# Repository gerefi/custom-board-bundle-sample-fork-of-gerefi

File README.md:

<div align="center">

<b>GPL open-source ECU</b>

</div>

# gerefi

See [check.c](https://github.com/gerefi/gerefi/blob/master/firmware/check.c) for recommended version of GCC.

Current binaries are always available on our [build server](http://gerefi.com/build_server/)

# Cloning the repository
`git clone https://github.com/gerefi/gerefi.git`
Important note - we now use submodules:

`git submodule update --init`

# What do we have here?
 * [Firmware](/firmware) Source code for open source engine control unit for stm32 chips incuding [implementation overview](https://github.com/gerefi/gerefi/blob/master/firmware/readme.md)
 * [Hardware](/hardware) KiCAD files for our older PCBs
 * [gerefi console](/java_console) gerefi own naive tuning software
 * [Simulator](/simulator) win32 or posix version of firmware allows to explore without any hardware 
 * [Unit Tests](/unit_tests) Unit tests of firmware pieces
 * [Misc tools](/java_tools) Misc development utilities
 * [misc/Jenkins](/misc/jenkins) Jenkins Continuous Integration scripts
 * [Software Development process](misc/SoftwareDevelopmentProcess.md)

# External Links

 * [Documentation](https://github.com/gerefi/gerefi/wiki)
 * [Doxygen documentation](http://gerefi.com/docs/html)
 * [General source code Q&A](http://gerefi.com/forum/viewtopic.php?f=5&t=10)
 * [Facebook](https://www.facebook.com/gerefiECU)

# Building the Code
Check out https://gerefi.com/forum/viewtopic.php?f=5&t=9

# Release Notes

See [the changelog](firmware/CHANGELOG.md)

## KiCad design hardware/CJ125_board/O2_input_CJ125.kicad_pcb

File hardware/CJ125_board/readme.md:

[iBom](https://gerefi.com/docs/ibom/O2_input_CJ125_latest.html)

2019 status: known to work, but documentation is very limited :(

On this board UR and UA do NOT have build-in resistor dividers.

There is an opinion that for open air UA divider is required.

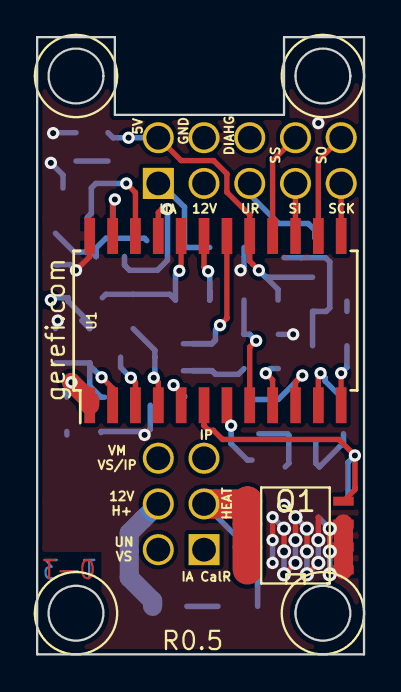
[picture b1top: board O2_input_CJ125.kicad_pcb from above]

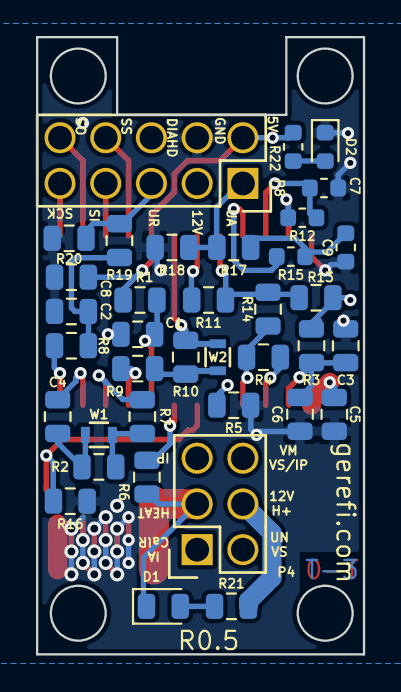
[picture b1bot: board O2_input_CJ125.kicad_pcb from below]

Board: 4 copper layers, 18.2 x 34.3 mm, 39 parts (37 on the bottom side), 35 nets.

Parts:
C1: 1000pF; C_0805_2012Metric
C2, C6, C8: 0.033uF; C_0805_2012Metric
C3: DNP; C_0805_2012Metric
C4: 0.1uF; C_0805_2012Metric
C5: 220pf; C_0805_2012Metric
C7: 0.1uF; C_0603_1608Metric
C9: 0.033uF; C_0603_1608Metric
D1: LED-RED; LED_0805_2012Metric
D2: LED-GRN; LED_0603_1608Metric
P4: CONN_02X03; Socket_Strip_Straight_2x03
P8: CONN_02X05; Socket_Strip_Straight_2x05
Q1: FDS2734; SO8E_ST
R1, R5, R7, R16, R18, R20: 10k; R_0805_2012Metric
R2: 21k6; R_0805_2012Metric
R3: 0R; R_0805_2012Metric
R4: 61.9; R_0805_2012Metric
R6, R17, R19: 6.8k; R_0805_2012Metric
R8: 1k; R_0805_2012Metric
R9: 82.5; R_0805_2012Metric
R10: 220; R_0805_2012Metric
R11: 5.11k; R_0805_2012Metric
R12: 100k; R_0603_1608Metric
R13: 100k; R_0805_2012Metric
R14: 511k; R_0805_2012Metric
R15, R22: 1k; R_0603_1608Metric
R21: 4.7k; R_0805_2012Metric
U1: CJ125; SOIC-24_7.5x15.4mm_Pitch1.27mm
W1, W2: TEST; R_0603

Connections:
/CF: C7.2, R12.1, U1.22
/CJ125_5v: C8.2, P8.2, R1.2, R22.1, U1.17
/CJ125_HEATER: D1.1, P4.3, Q1.2, R6.2
/CJ125_IA: P4.1, R4.2, R14.1, U1.4
/CJ125_IP: P4.5, R4.1, U1.3
/CJ125_SCK: P8.9, U1.13
/CJ125_SI: P8.7, U1.15
/CJ125_SO: P8.10, U1.14
/CJ125_SS: P8.8, U1.16
/CJ125_UA: C9.2, R15.1, R17.2
/CJ125_UN: P4.2, R3.2, R13.1
/CJ125_UR: C2.1, R8.2, R19.2
/CJ125_VM: P4.6, R10.1, U1.18, W2.2
/CM: C4.2, U1.11
/DIAHD: R6.1, U1.7
/DIAHG: P8.6, Q1.1, R16.2, U1.6
/OSZ: R5.2, U1.5
/RF: R12.2, U1.23
/RM: R7.1, U1.10
/RS: R9.2, U1.9
/RST: C1.1, R1.1, U1.8
/UA: R15.2, U1.21
/UN: C3.1, C5.1, R3.1, U1.2
/UP: R11.1, R13.2, R14.2, U1.20
/UR: R8.1, U1.12
/US: R11.2, U1.19
/WO2-12V: C6.2, P4.4, P8.3, R21.2, U1.1
GND: C1.2, C2.2, C3.2, C5.2, C6.1, C7.1, C8.1, C9.1, D2.1, P8.4, Q1.3, R5.1, R16.1, R18.2, R20.2, U1.24
unnamed: C4.1, R2.2, W1.1
unnamed: D1.2, R21.1
unnamed: D2.2, R22.2
unnamed: P8.1, R17.1, R18.1
unnamed: P8.5, R19.1, R20.1
unnamed: R2.1, R7.2, W1.2
unnamed: R9.1, R10.2, W2.1

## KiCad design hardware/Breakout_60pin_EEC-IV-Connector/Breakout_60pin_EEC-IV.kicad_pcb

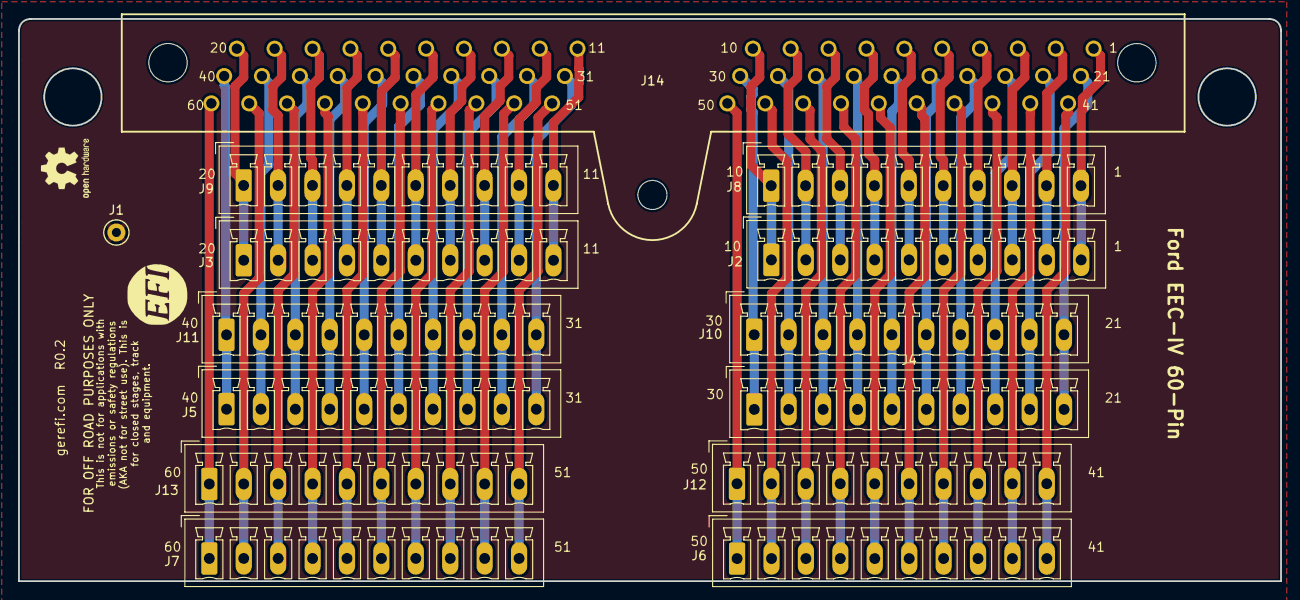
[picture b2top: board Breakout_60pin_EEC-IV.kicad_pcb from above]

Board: 2 copper layers, 139.7 x 62.2 mm, 17 parts (0 on the bottom side), 60 nets.

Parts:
G1: Disclaimer; Off_Road_Disclaimer
G2: LOGO
J1: Conn_01x01; TestPoint_Keystone_5000-5004_Miniature
J2, J3, J4, J5, J6, J7, J8, J9, J10, J11, J12, J13: Conn_01x10; PhoenixContact_MCV_1,5_10-G-3.81_1x10_P3.81mm_Vertical
J14: EEC-IV; eeciv
LOGO1: DNP; OSHW-Logo2_7.3x6mm_SilkScreen

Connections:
/1: J2.10, J8.10, J14.1
/5: J2.6, J8.6, J14.5
/10: J2.1, J8.1, J14.10
/11: J3.10, J9.10, J14.11
/15: J3.6, J9.6, J14.15
/25: J4.6, J10.6, J14.25
/30: J4.1, J10.1, J14.30
/31: J5.10, J11.10, J14.31
/35: J5.6, J11.6, J14.35
/40: J5.1, J11.1, J14.40
/41: J6.10, J12.10, J14.41
/45: J6.6, J12.6, J14.45
/50: J6.1, J12.1, J14.50
/53: J7.8, J13.8, J14.53
/54: J7.7, J13.7, J14.54
/55: J7.6, J13.6, J14.55
/60: J7.1, J13.1, J14.60
/420: J3.1, J9.1, J14.20
/421: J4.10, J10.10, J14.21
unnamed: J4.2, J10.2, J14.29
unnamed: J4.3, J10.3, J14.28
unnamed: J4.4, J10.4, J14.27
unnamed: J4.5, J10.5, J14.26
unnamed: J4.7, J10.7, J14.24
unnamed: J4.8, J10.8, J14.23
unnamed: J4.9, J10.9, J14.22
unnamed: J5.2, J11.2, J14.39
unnamed: J5.3, J11.3, J14.38
unnamed: J5.4, J11.4, J14.37
unnamed: J5.5, J11.5, J14.36
unnamed: J5.7, J11.7, J14.34
unnamed: J5.8, J11.8, J14.33
unnamed: J5.9, J11.9, J14.32
unnamed: J6.2, J12.2, J14.49
unnamed: J6.3, J12.3, J14.48
unnamed: J6.4, J12.4, J14.47
unnamed: J6.5, J12.5, J14.46
unnamed: J6.7, J12.7, J14.44
unnamed: J6.8, J12.8, J14.43
unnamed: J6.9, J12.9, J14.42
unnamed: J7.2, J13.2, J14.59
unnamed: J7.3, J13.3, J14.58
unnamed: J7.4, J13.4, J14.57
unnamed: J7.5, J13.5, J14.56
unnamed: J7.9, J13.9, J14.52
unnamed: J7.10, J13.10, J14.51
unnamed: J2.9, J8.9, J14.2
unnamed: J2.8, J8.8, J14.3
unnamed: J2.7, J8.7, J14.4
unnamed: J2.5, J8.5, J14.6
unnamed: J2.4, J8.4, J14.7
unnamed: J2.3, J8.3, J14.8
unnamed: J2.2, J8.2, J14.9
unnamed: J3.9, J9.9, J14.12
unnamed: J3.8, J9.8, J14.13
unnamed: J3.7, J9.7, J14.14
unnamed: J3.5, J9.5, J14.16
unnamed: J3.4, J9.4, J14.17
unnamed: J3.3, J9.3, J14.18
unnamed: J3.2, J9.2, J14.19

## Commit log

2024-03-10 Bump actions/checkout from 3 to 4
    Bumps [actions/checkout](https://github.com/actions/checkout) from 3 to 4.
    - [Release notes](https://github.com/actions/checkout/releases)
    - [Changelog](https://github.com/actions/checkout/blob/main/CHANGELOG.md)
    - [Commits](https://github.com/actions/checkout/compare/v3...v4)
    ---
    updated-dependencies:
2024-03-10 Bump actions/upload-artifact from 3 to 4
    Bumps [actions/upload-artifact](https://github.com/actions/upload-artifact) from 3 to 4.
    - [Release notes](https://github.com/actions/upload-artifact/releases)
    - [Commits](https://github.com/actions/upload-artifact/compare/v3...v4)
    ---
    updated-dependencies:
    - dependency-name: actions/upload-artifact
2024-03-10 Bump actions/setup-java from 3 to 4
    Bumps [actions/setup-java](https://github.com/actions/setup-java) from 3 to 4.
    - [Release notes](https://github.com/actions/setup-java/releases)
    - [Commits](https://github.com/actions/setup-java/compare/v3...v4)
    ---
    updated-dependencies:
    - dependency-name: actions/setup-java
2024-03-10 Bump mukunku/tag-exists-action from 1.2.0 to 1.6.0
    Bumps [mukunku/tag-exists-action](https://github.com/mukunku/tag-exists-action) from 1.2.0 to 1.6.0.
    - [Release notes](https://github.com/mukunku/tag-exists-action/releases)
    - [Commits](https://github.com/mukunku/tag-exists-action/compare/v1.2.0...v1.6.0)
    ---
    updated-dependencies:
    - dependency-name: mukunku/tag-exists-action
2024-03-10 Bump ncipollo/release-action from 1.12.0 to 1.14.0
    Bumps [ncipollo/release-action](https://github.com/ncipollo/release-action) from 1.12.0 to 1.14.0.
    - [Release notes](https://github.com/ncipollo/release-action/releases)
    - [Commits](https://github.com/ncipollo/release-action/compare/v1.12.0...v1.14.0)
    ---
    updated-dependencies:
    - dependency-name: ncipollo/release-action
2024-03-10 Bump chuckwagoncomputing/interactive-pinout from 2.4 to 2.14
    Bumps [chuckwagoncomputing/interactive-pinout](https://github.com/chuckwagoncomputing/interactive-pinout) from 2.4 to 2.14.
    - [Release notes](https://github.com/chuckwagoncomputing/interactive-pinout/releases)
    - [Commits](https://github.com/chuckwagoncomputing/interactive-pinout/compare/2.4...2.14)
    ---
    updated-dependencies:
    - dependency-name: chuckwagoncomputing/interactive-pinout
